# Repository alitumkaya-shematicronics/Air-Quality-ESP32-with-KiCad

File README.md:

# Air-Quality-ESP32-with-KiCad
* Basic ESP32 Air Quality PCB with AliTumkaya

# Shematic

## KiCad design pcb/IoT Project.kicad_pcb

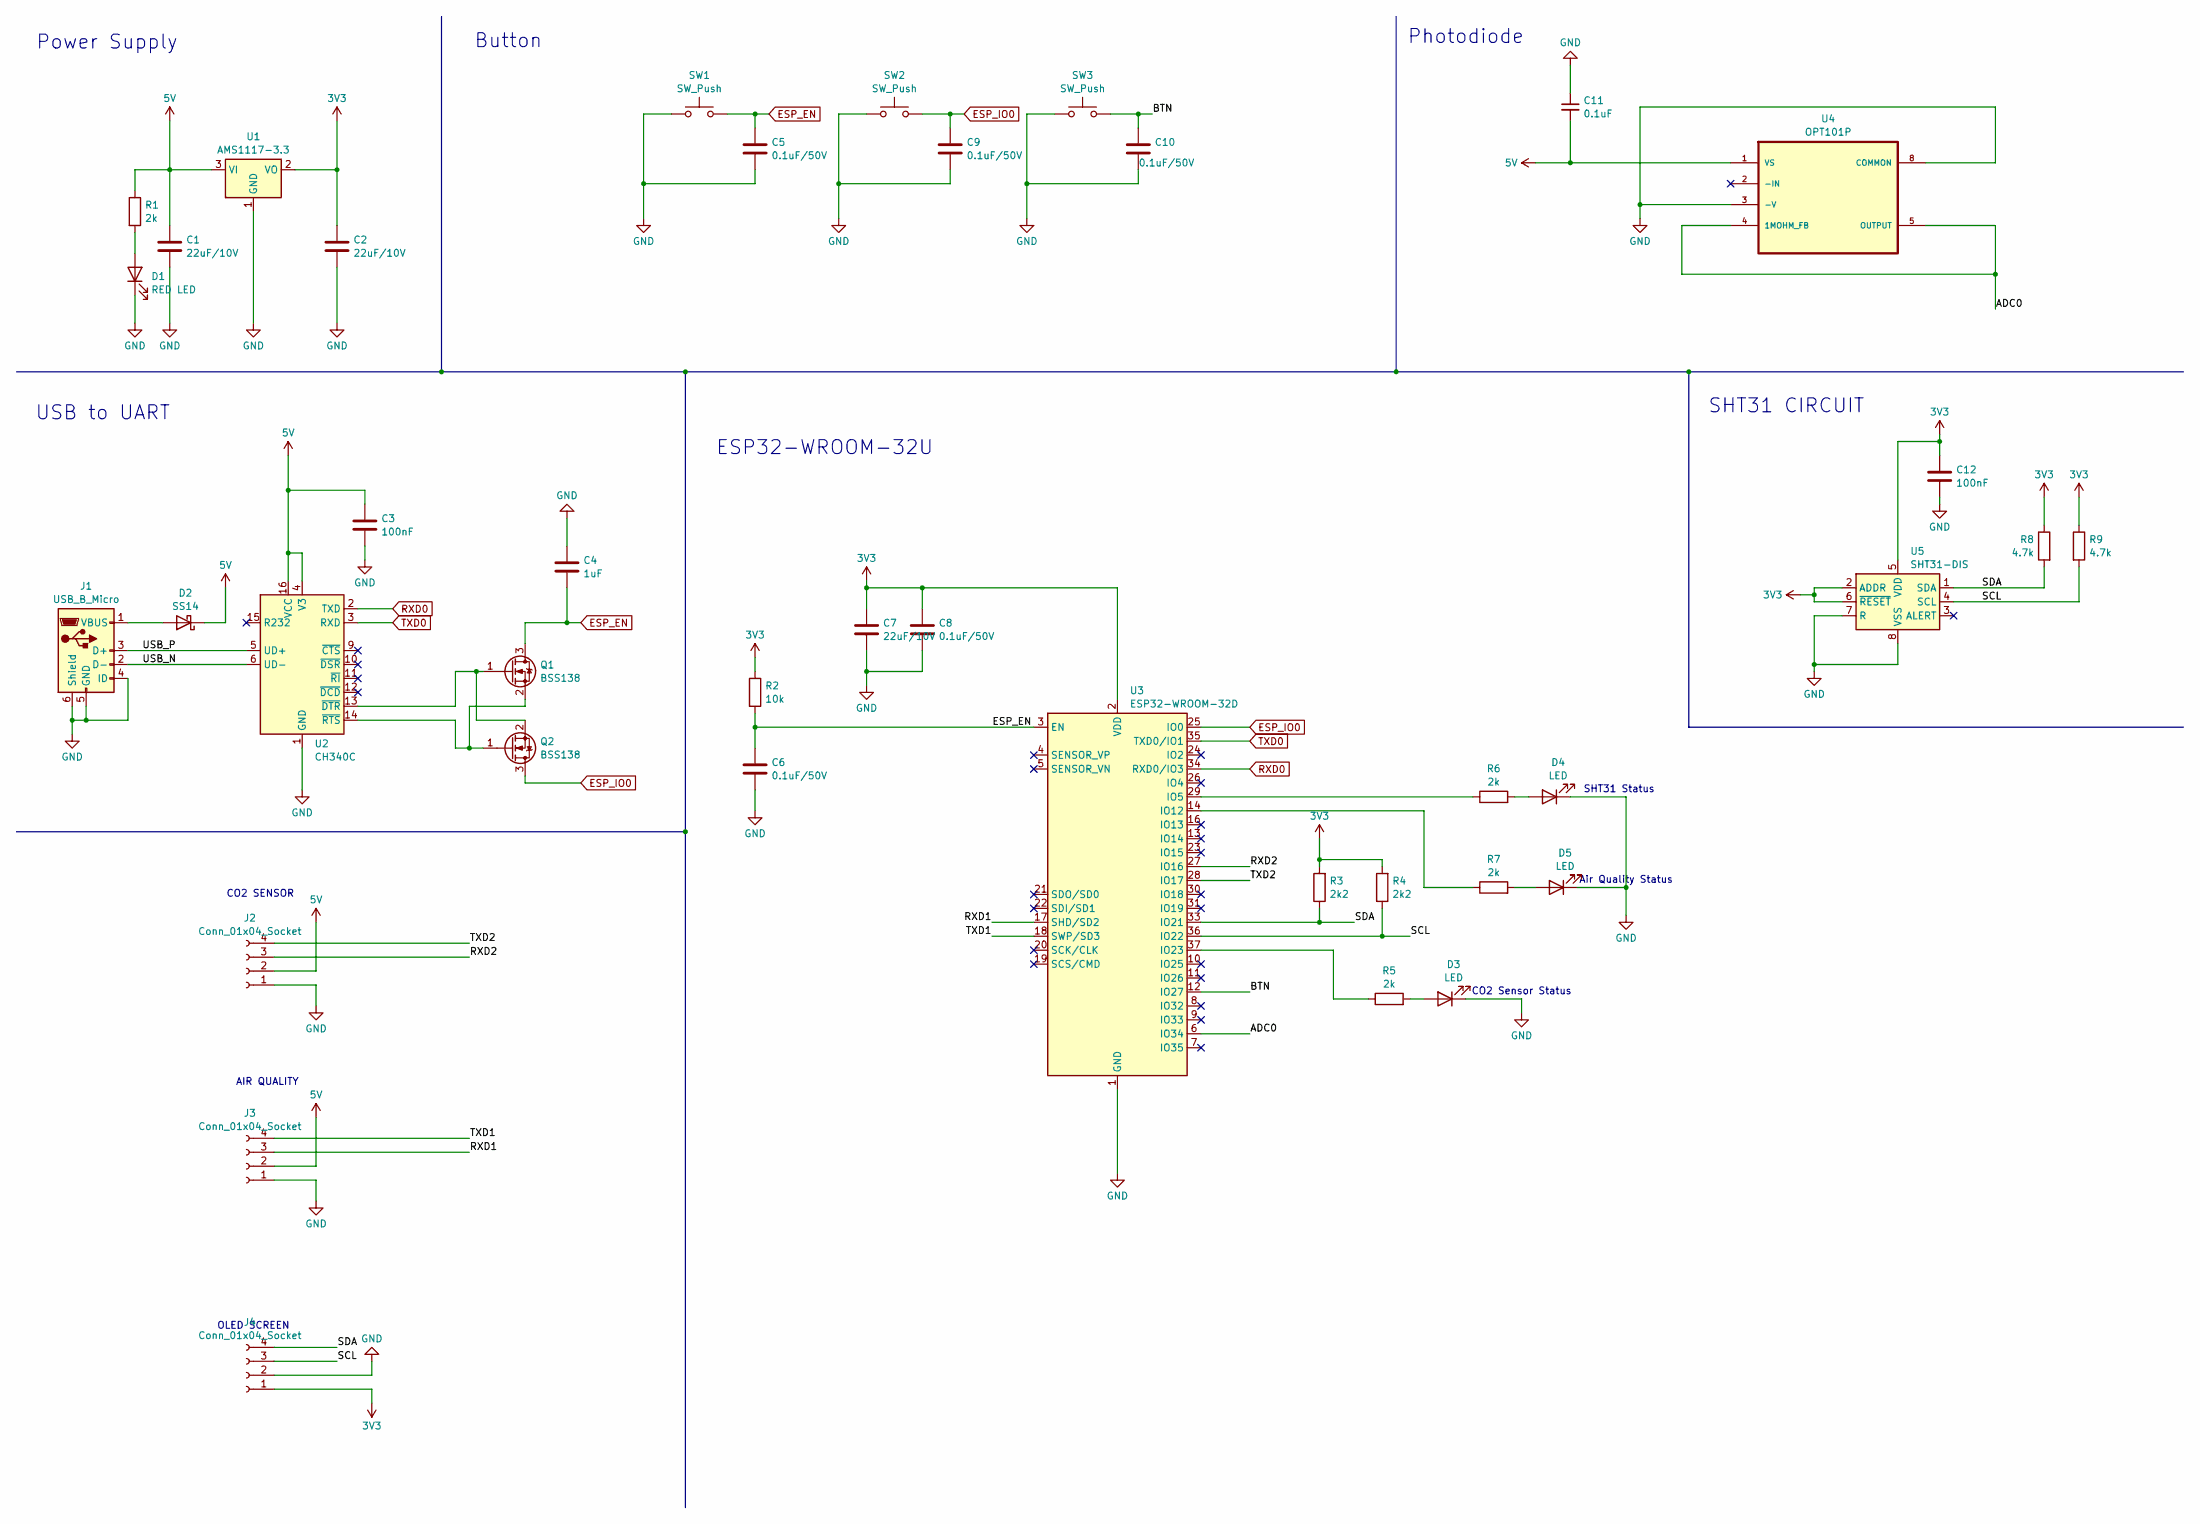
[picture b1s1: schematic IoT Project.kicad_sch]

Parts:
C1, C2, C7: 22uF/10V; C_0805_2012Metric
C3, C12: 100nF; C_0805_2012Metric
C4: 1uF; C_0805_2012Metric
C5, C6, C8, C9, C10: 0.1uF/50V; C_0805_2012Metric
C11: 0.1uF; C_0805_2012Metric_Pad1.18x1.45mm_HandSolder
D1: RED LED; LED_0805_2012Metric
D2: SS14; D_SMA
D3, D4, D5: LED; LED_0805_2012Metric
J1: USB_B_Micro; SAMTEC_MUSB-05-X-AB-SM-A
J2, J3, J4: Conn_01x04_Socket; PinSocket_1x04_P2.54mm_Vertical
Q1, Q2: BSS138; SOT-23
R1, R5, R6, R7: 2k; R_0805_2012Metric
R2: 10k; R_0805_2012Metric
R3, R4: 2k2; R_0805_2012Metric
R8, R9: 4.7k; R_0805_2012Metric
SW1, SW2, SW3: SW_Push; SW_PUSH_6mm
U1: AMS1117-3.3; SOT-223-3_TabPin2
U2: CH340C; SOIC-16_3.9x9.9mm_P1.27mm
U3: ESP32-WROOM-32D
U4: OPT101P; DIP762W46P254L952H419Q8
U5: SHT31-DIS; Sensirion_DFN-8-1EP_2.5x2.5mm_P0.5mm_EP1.1x1.7mm

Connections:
3V3: C2.1, C7.2, C8.2, C12.2, J4.1, R2.1, R3.2, R4.2, R8.1, R9.1, U1.2 (VO), U3.2 (VDD), U5.2 (ADDR), U5.5 (VDD), U5.6 (~RESET)
5V: C1.1, C3.1, C11.2, D2.1 (K), J2.2, J3.2, R1.1, U1.3 (VI), U2.4 (V3), U2.16 (VCC), U4.1 (VS)
/ADC0: U3.6 (IO34), U4.4 (1MOHM_FB), U4.5 (OUTPUT)
/BTN: C10.2, SW3.2, U3.12 (IO27)
/RXD1: J3.3, U3.17 (SHD/SD2)
/RXD2: J2.3, U3.27 (IO16)
/SCL: J4.3, R4.1, R9.2, U3.36 (IO22), U5.4 (SCL)
/SDA: J4.4, R3.1, R8.2, U3.33 (IO21), U5.1 (SDA)
/TXD1: J3.4, U3.18 (SWP/SD3)
/TXD2: J2.4, U3.28 (IO17)
/USB_N: J1.2 (D-), U2.6 (UD-)
/USB_P: J1.3 (D+), U2.5 (UD+)
ESP_EN: C4.2, C5.2, C6.2, Q1.3 (D), R2.2, SW1.2, U3.3 (EN)
ESP_IO0: C9.2, Q2.3 (D), SW2.2, U3.25 (IO0)
GND: C1.2, C2.2, C3.2, C4.1, C5.1, C6.1, C7.1, C8.1, C9.1, C10.1, C11.1, C12.1, D1.1 (K), D3.1 (K), D4.1 (K), D5.1 (K), J1.4 (ID), J1.5 (GND), J1.6 (Shield), J2.1, J3.1, J4.2, SW1.1, SW2.1, SW3.1, U1.1 (GND), U2.1 (GND), U3.1 (GND), U3.15 (GND), U3.38 (GND), U3.39 (GND), U4.3 (-V), U4.8 (COMMON), U5.7 (R), U5.8 (VSS), U5.9 (VSS)
unnamed: D1.2 (A), R1.2
unnamed: D2.2 (A), J1.1 (VBUS)
unnamed: D3.2 (A), R5.2
unnamed: D4.2 (A), R6.2
unnamed: D5.2 (A), R7.2
unnamed: Q1.1 (G), Q2.2 (S), U2.13 (~DTR)
unnamed: Q1.2 (S), Q2.1 (G), U2.14 (~RTS)
unnamed: R6.1, U3.29 (IO5)
unnamed: R7.1, U3.14 (IO12)
unnamed: R5.1, U3.37 (IO23)
RXD0: U2.2 (TXD), U3.34 (RXD0/IO3)
TXD0: U2.3 (RXD), U3.35 (TXD0/IO1)

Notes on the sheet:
USB to UART
ESP32-WROOM-32U
Air Quality Status
AIR QUALITY
Button
CO2 Sensor Status
OLED SCREEN
SHT31 Status
CO2 SENSOR
SHT31 CIRCUIT
Photodiode
Power Supply

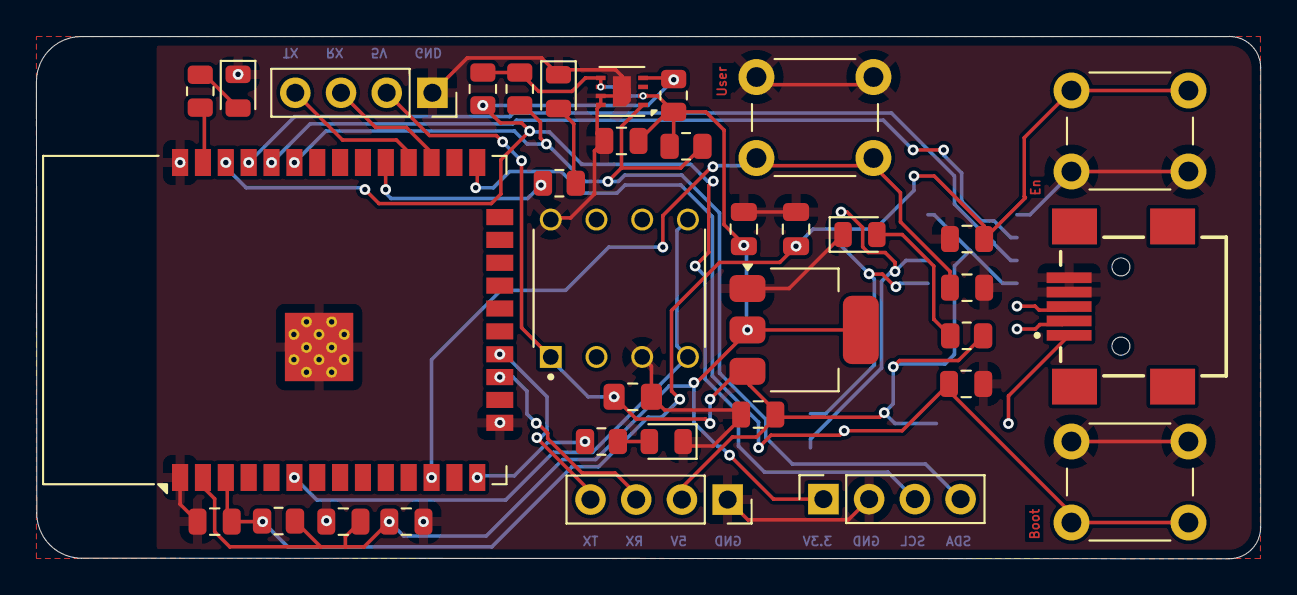
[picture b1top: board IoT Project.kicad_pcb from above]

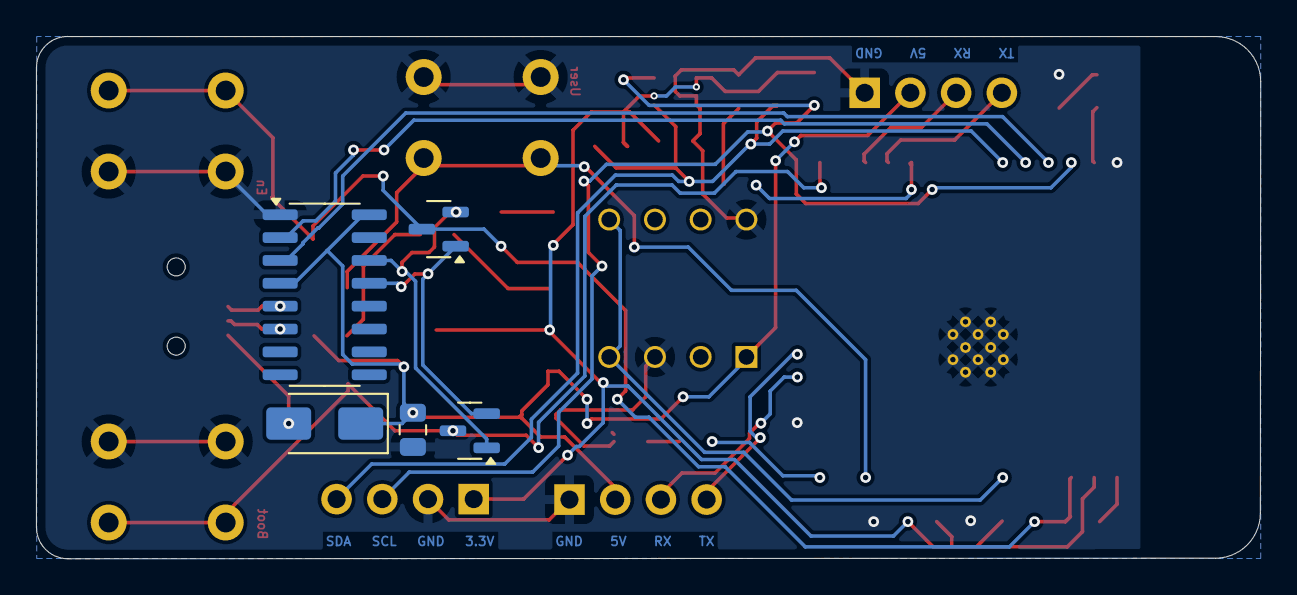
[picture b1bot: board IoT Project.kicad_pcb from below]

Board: 2 copper layers, 68.0 x 29.0 mm, 40 parts (5 on the bottom side), 27 nets.

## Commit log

2025-01-11 Air-Quality-ESP32-with-KiCad
    Air-Quality-ESP32-with-KiCad
